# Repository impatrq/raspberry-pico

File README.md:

# raspberry-pico
Repositorio con material sobre la Raspberry Pico

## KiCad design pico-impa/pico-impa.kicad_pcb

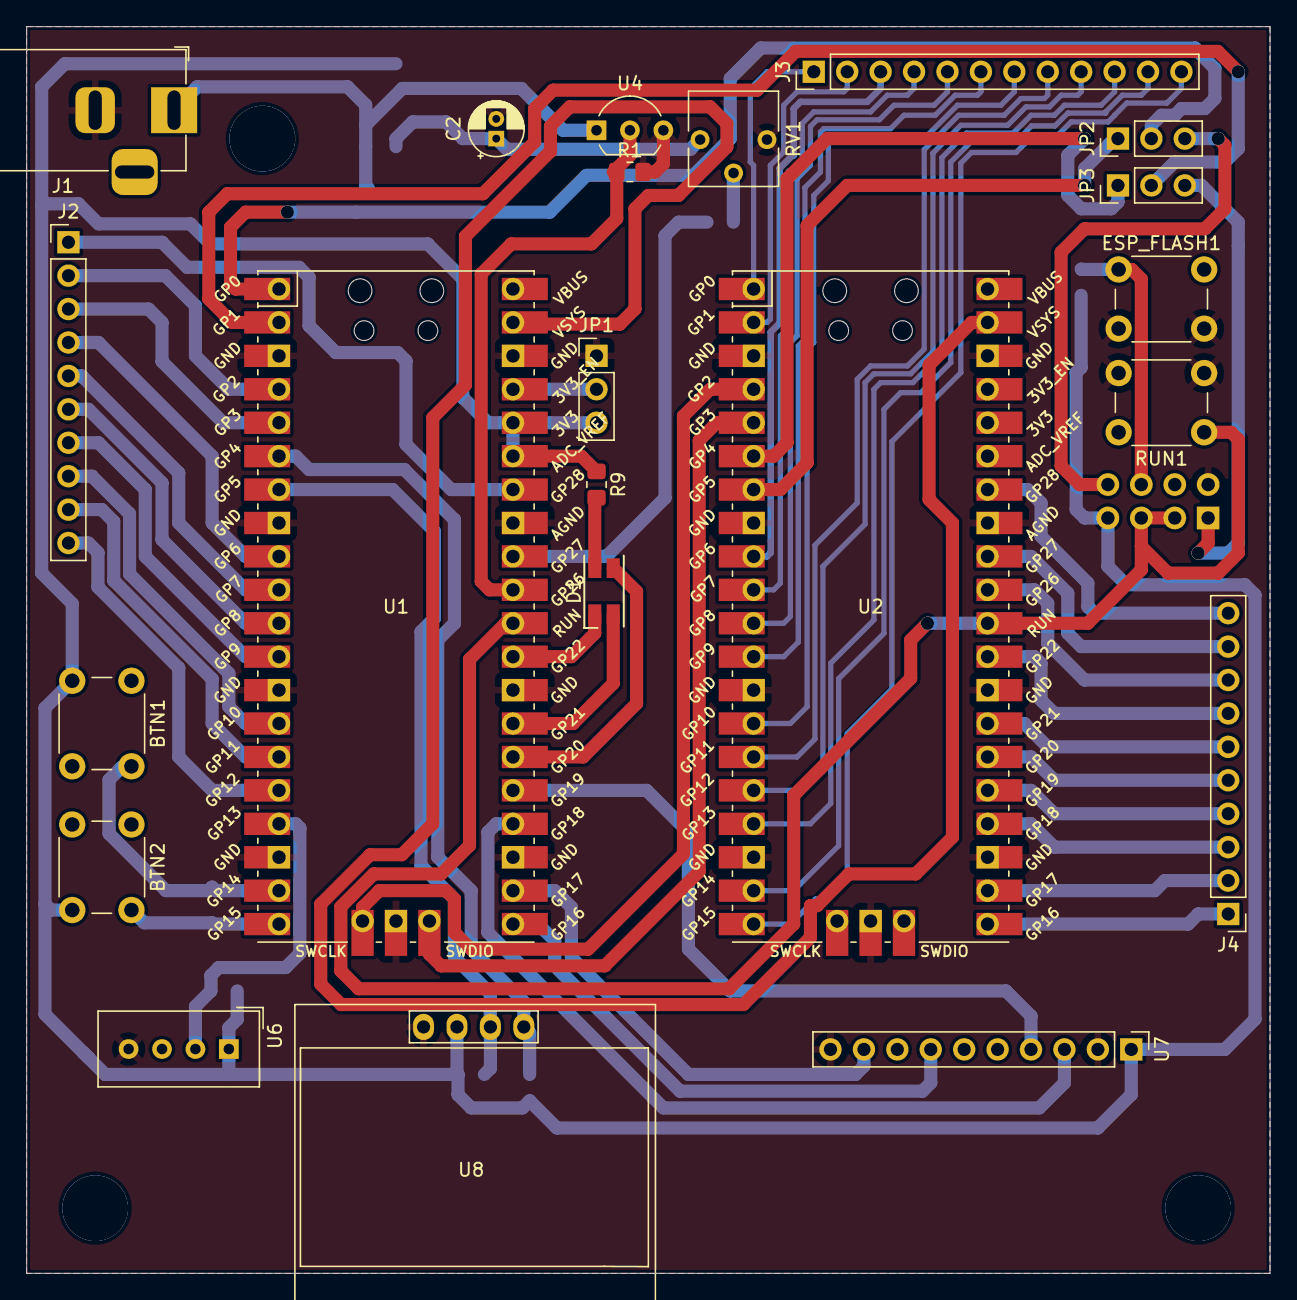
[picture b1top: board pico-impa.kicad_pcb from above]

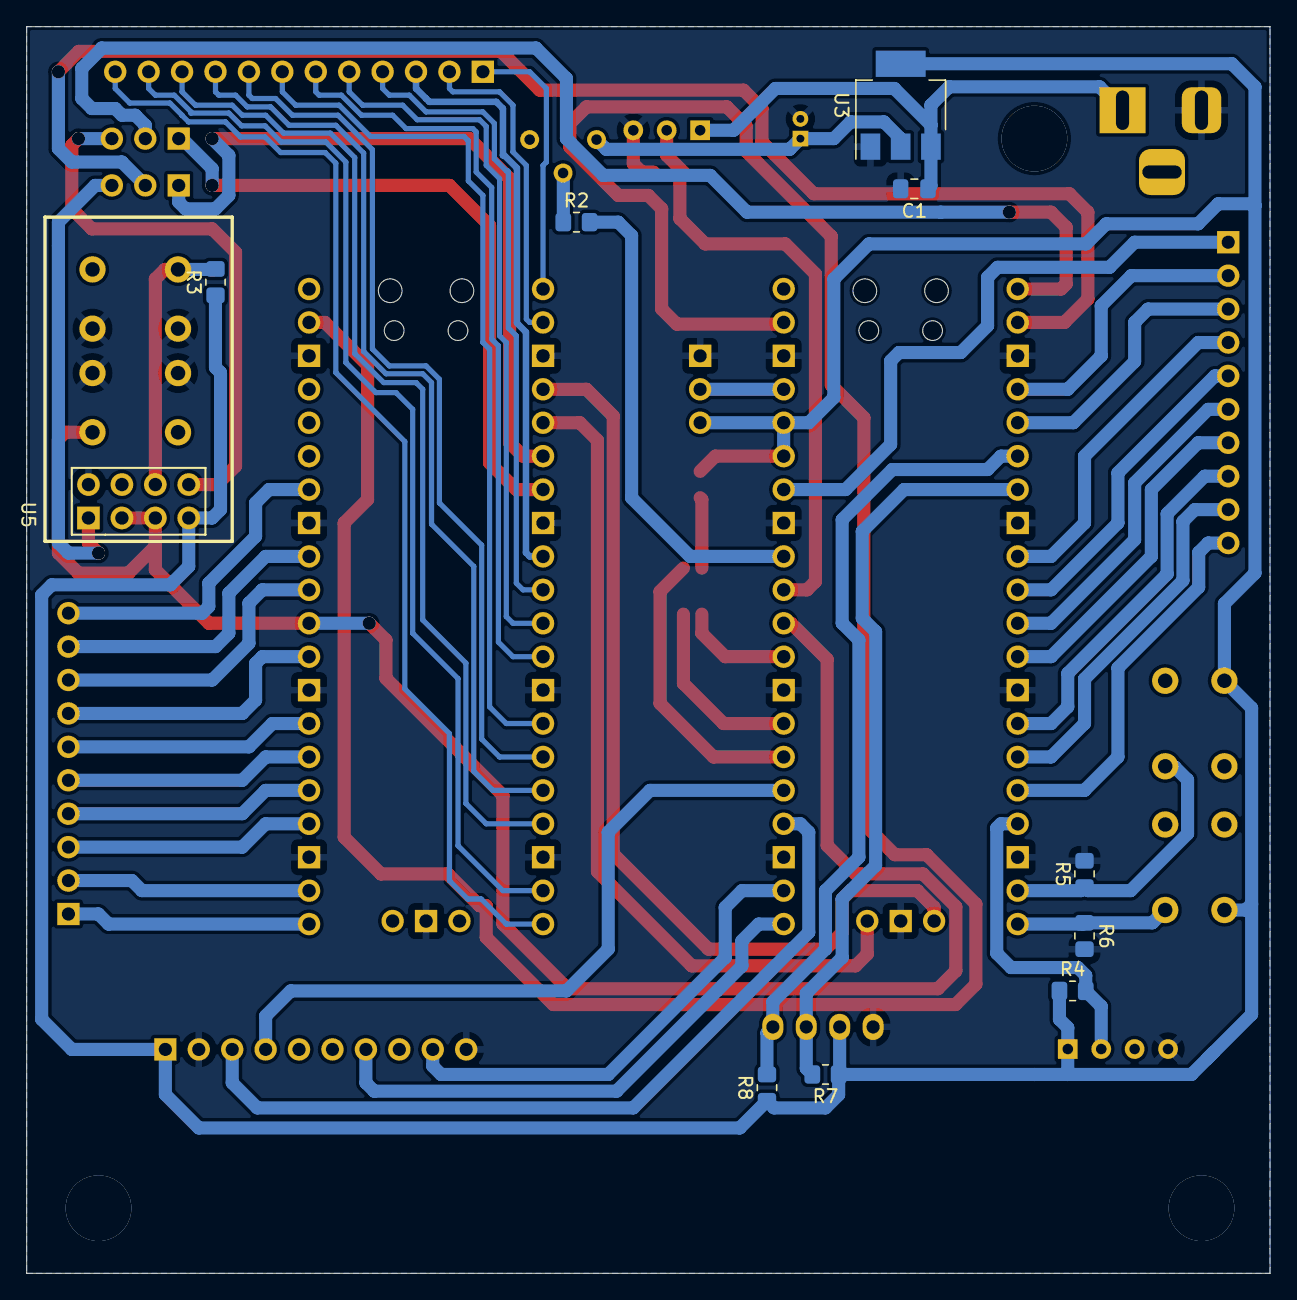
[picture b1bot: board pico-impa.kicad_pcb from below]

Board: 2 copper layers, 94.5 x 94.7 mm, 32 parts (10 on the bottom side), 64 nets.

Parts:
BTN1, BTN2: SW_Push; SW_PUSH_6mm_H5mm
C1: 10u; C_0805_2012Metric_Pad1.18x1.45mm_HandSolder
C2: 10u; CP_Radial_D4.0mm_P1.50mm
D1: LED_RGBA; LED_RGB_1210
ESP_FLASH1: SW_Push; SW_PUSH_6mm_H5mm
J1: Barrel_Jack_MountingPin; BarrelJack_Horizontal
J2, J4: Conn_01x10; PinHeader_1x10_P2.54mm_Vertical
J3: Conn_01x12; PinHeader_1x12_P2.54mm_Vertical
JP1, JP2, JP3: Conn_01x03; PinHeader_1x03_P2.54mm_Vertical
R1: 1K; R_0805_2012Metric_Pad1.20x1.40mm_HandSolder
R2: 100; R_0805_2012Metric_Pad1.20x1.40mm_HandSolder
R3, R5, R6: 10K; R_0805_2012Metric_Pad1.20x1.40mm_HandSolder
R4, R7, R8: 4K7; R_0805_2012Metric_Pad1.20x1.40mm_HandSolder
R9: 330; R_0805_2012Metric_Pad1.20x1.40mm_HandSolder
RUN1: SW_Push; SW_PUSH_6mm_H5mm
RV1: R_Potentiometer; Potentiometer_Vishay_T73YP_Vertical
U1: Raspberry Pi Pico; RPi_Pico_SMD_TH
U2: Rasbperry Pi Pico Probe; RPi_Pico_SMD_TH
U3: AMS1117-3.3; SOT-223-3_TabPin2
U4: LM35-LP; TO-92_Inline_Wide
U5: ESP-01
U6: DHT11; Aosong_DHT11_5.5x12.0_P2.54mm
U7: MPU9250; PinHeader_1x10_P2.54mm_Vertical
U8: SSD1306; 128x64OLED

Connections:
+3V3: BTN1.2, BTN2.2, C2.1, JP1.3, R3.1, R4.1, R7.1, R8.1, R9.1, RV1.1, U1.35 (ADC_VREF), U1.36 (3V3), U3.2 (VO), U5.7 (VCC), U6.1 (VCC), U7.1 (VCC), U8.2 (VCC)
/ESP_FLASH: ESP_FLASH1.1, R3.2, U5.6 (GPIO0)
/ESP_RX: JP2.3, U5.8 (URXD)
/ESP_TX: JP3.3, U5.1 (UTXD)
/PICO_ADC0: R1.1, U1.31 (GPIO26_ADC0), U4.2 (Vout)
/PICO_ADC1: R2.2, U1.32 (GPIO27_ADC1)
/PICO_BLED: D1.3 (BK), U1.26 (GPIO20)
/PICO_BTN1: BTN1.1, R5.1, U1.19 (GPIO14)
/PICO_BTN2: BTN2.1, R6.1, U1.20 (GPIO15)
/PICO_DHT11: R4.2, U1.17 (GPIO13), U6.2 (IO)
/PICO_GLED: D1.2 (GK), U1.27 (GPIO21)
/PICO_GPIO2: J2.2, U1.4 (GPIO2)
/PICO_GPIO3: J2.3, U1.5 (GPIO3)
/PICO_GPIO6: J2.4, U1.9 (GPIO6)
/PICO_GPIO7: J2.5, U1.10 (GPIO7)
/PICO_GPIO8: J2.6, U1.11 (GPIO8)
/PICO_GPIO9: J2.7, U1.12 (GPIO9)
/PICO_GPIO10: J2.8, U1.14 (GPIO10)
/PICO_GPIO11: J2.9, U1.15 (GPIO11)
/PICO_GPIO12: J2.10, U1.16 (GPIO12)
/PICO_GPIO28: J2.1, U1.34 (GPIO28_ADC2)
/PICO_I2C0_SCL: R7.2, U1.7 (GPIO5), U8.3 (SCL)
/PICO_I2C0_SDA: R8.2, U1.6 (GPIO4), U8.4 (SDA)
/PICO_RLED: D1.1 (RK), U1.29 (GPIO22)
/PICO_SPI0_CSn: U1.22 (GPIO17), U7.9 (NCS)
/PICO_SPI0_RX: U1.21 (GPIO16), U7.7 (AD0/SDO)
/PICO_SPI0_SCK: U1.24 (GPIO18), U7.3 (SCL/SCLK)
/PICO_SPI0_TX: U1.25 (GPIO19), U7.4 (SDA/SDI)
/PICO_UART0_RX: JP3.2, U1.2 (GPIO1)
/PICO_UART0_TX: JP2.2, U1.1 (GPIO0)
/PROBE_GPIO0: J3.1, U2.1 (GPIO0)
/PROBE_GPIO1: J3.2, U2.2 (GPIO1)
/PROBE_GPIO6: J3.3, U2.9 (GPIO6)
/PROBE_GPIO7: J3.4, U2.10 (GPIO7)
/PROBE_GPIO8: J3.5, U2.11 (GPIO8)
/PROBE_GPIO9: J3.6, U2.12 (GPIO9)
/PROBE_GPIO10: J3.7, U2.14 (GPIO10)
/PROBE_GPIO11: J3.8, U2.15 (GPIO11)
/PROBE_GPIO12: J3.9, U2.16 (GPIO12)
/PROBE_GPIO13: J3.10, U2.17 (GPIO13)
/PROBE_GPIO14: J3.11, U2.19 (GPIO14)
/PROBE_GPIO15: J3.12, U2.20 (GPIO15)
/PROBE_GPIO16: J4.1, U2.21 (GPIO16)
/PROBE_GPIO17: J4.2, U2.22 (GPIO17)
/PROBE_GPIO18: J4.3, U2.24 (GPIO18)
/PROBE_GPIO19: J4.4, U2.25 (GPIO19)
/PROBE_GPIO20: J4.5, U2.26 (GPIO20)
/PROBE_GPIO21: J4.6, U2.27 (GPIO21)
/PROBE_GPIO22: J4.7, U2.29 (GPIO22)
/PROBE_GPIO26: J4.8, U2.31 (GPIO26_ADC0)
/PROBE_GPIO27: J4.9, U2.32 (GPIO27_ADC1)
/PROBE_GPIO28: J4.10, U2.34 (GPIO28_ADC2)
/PROBE_RX: JP2.1, U2.7 (GPIO5)
/PROBE_SWCLK: U1.41 (SWCLK), U2.4 (GPIO2)
/PROBE_SWDIO: U1.43 (SWDIO), U2.5 (GPIO3)
/PROBE_TX: JP3.1, U2.6 (GPIO4)
/RUN: RUN1.1, U1.30 (RUN), U2.30 (RUN), U5.3 (CH_PD), U5.5 (RST)
/VSYSB: U1.39 (VSYS), U2.39 (VSYS)
GND: C1.2, C2.2, ESP_FLASH1.2, J1.2, JP1.1, R1.2, R5.2, R6.2, RUN1.2, RV1.3, U1.3 (GND), U1.8 (GND), U1.13 (GND), U1.18 (GND), U1.23 (GND), U1.28 (GND), U1.33 (AGND), U1.38 (GND), U1.42 (GND), U2.3 (GND), U2.8 (GND), U2.13 (GND), U2.18 (GND), U2.23 (GND), U2.28 (GND), U2.33 (AGND), U2.38 (GND), U2.42 (GND), U3.1 (GND), U4.3 (GND), U5.2 (GND), U6.4 (GND), U7.2 (GND), U7.10 (FSYNC), U8.1 (GND)
unnamed: D1.4 (A), R9.2
unnamed: JP1.2, U1.37 (3V3_EN)
unnamed: R2.1, RV1.2
unnamed: U2.35 (ADC_VREF), U2.36 (3V3)
VDC: C1.1, J1.1, U3.3 (VI), U4.1 (+VS)

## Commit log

2022-04-26 feat: add main, CMakeLists and build directory
2022-04-26 fix: more generic CMakeLists
2022-04-26 docs: add README with directory info
2022-04-26 docs: add mkdir build instruction
2022-04-26 feat: add uf2 files
2022-04-26 docs: add content info
2022-04-28 feat: add examples from raspberry repo
2022-04-28 fix: add examples
2022-04-30 feat: add .gitignore
2022-04-30 feat: kicad project created
2022-04-30 feat: add pico libraries
2022-04-30 feat: add esp libraries
2022-04-30 feat: add OLED library
2022-04-30 feat: first schematic version
2022-05-03 fix: fix cmake command
2022-05-04 feat: update schematic
2022-05-04 feat: add adc multicore example
2022-05-04 feat: adc_multicore example
2022-05-04 docs: docs folder added
2022-05-05 docs: add reference to adc_multicore
2022-05-13 feat: add pwm fade example
2022-05-18 feat: schematic finished without gnd layer
2022-05-18 feat: multicore example with queue
2022-05-18 feat: pcb v1 finished
2022-05-18 feat: add freertos kernel for pico
2022-05-18 feat: add CMakeLists template
2022-05-18 feat: add main template
2022-05-18 feat: add freertos blinky example
2022-05-18 feat: change project name
2022-05-18 feat: add freertos blinky reference
2022-05-19 feat: add temperature sensor example
2022-05-19 feat: add freertos temperature sensor reference
2022-05-19 fix: enable usb stdio
2022-05-19 Feat/freertos (#1)
    * feat: add freertos kernel for pico
    * feat: add CMakeLists template
    * feat: add main template
    * feat: add freertos blinky example
    * feat: change project name
    * feat: add freertos blinky reference
2022-08-18 add readme for header files
2022-08-18 add readme for lib source files
2022-08-18 add header template and reference in readme
2022-08-18 add source file template and reference in main
2022-08-18 remove template files
2022-08-18 add rules to build libraries
2022-08-18 remove pdf files and reference documentation from raspberry site
2022-08-20 add compiling instructions for linux
2022-08-20 change directory name
2022-09-09 ignore .vscode directory
2022-09-09 add lib files
2022-09-09 added rules for lib
2022-09-09 add config struct and init function
2022-09-09 added register file
2022-09-09 init function and better config struct
2022-09-09 change enum name
2022-09-09 add write register function
2022-09-09 rename functions
2022-09-09 added read register function
2022-09-10 add clear and set register functions
2022-09-10 add command header
2022-09-10 add doc
2022-09-10 add soft reset function
2022-09-10 added docs
2022-09-10 added write function
2022-09-10 change cmd names
2022-09-10 added read function
2022-09-10 add firmware version enum
2022-09-10 add self test function
2022-09-10 fix read functions
2022-09-10 added get version function
2022-09-10 remove self test function
2022-09-10 add default init function
2022-09-10 add example
2022-09-10 add mfrc reference
2022-09-14 add launch configuration
2022-09-14 add settings for cmake
2022-09-14 disable usb output
2022-11-10 ejemplo comentado
2022-11-10 remuevo directorio vscode
2022-11-10 add readme
2022-11-10 move readme
2022-11-10 rfid reader library
2022-11-10 pinout
2022-11-10 reading example
2023-06-23 agrego ejemplos de platformio
2023-07-17 ignoro .DS_STORE
2023-07-17 agrego blinky baremetal
2023-09-22 elimino placa de desarrollo
2023-12-06 ejemplo de blinky en asm
2023-12-07 agrego firmware de pico-debug
2023-12-07 renombro funciones y agrego delay de 500 ms
2023-12-07 corrijo comentarios
2023-12-07 corrijo delay
